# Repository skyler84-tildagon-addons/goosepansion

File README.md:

# Goosepansion

*Tildagon Badge Hexpansion by Skyler84*

The **Goosepansion** hexpansion is a capacitive touch addon for the Tildagon badge. Additionally it is designed to be reversible - it can be inserted in either orientation to alter the behaviour of the hexpansion!

## **IMPORTANT**

The hardware of the original Goosepansion had some issues with the active electronics. This is being investigated and a bodge fix will hopefully be released soon!

## Hardware

The goosepansion contains some active electronics that are supposed to allow it to be inserted in either orientation. This is achieved by switching two pairs of pass-fets acting as level shifters and *should* allow the I2C bus to work in either orientation. This had some issues in the original board which is being tested and updated.

### BOM

- 2 * [DMG6602SVTQ-7 complementary PN mosfet pair](https://www.mouser.co.uk/ProductDetail/Diodes-Incorporated/DMG6602SVTQ-7?qs=s5XU71A7K7%252BjMAi7Ml65qw%3D%3D)
- 2 * [DMN63D8LDW-7 dual n-channel mosfet](https://www.mouser.co.uk/ProductDetail/Diodes-Incorporated/DMN63D8LDW-7?qs=wo71MgyKIyE2w30D2buODQ%3D%3D)
- 1 * [M24C64-RDW6TP 8KB I2C EEPROM](https://www.mouser.co.uk/ProductDetail/STMicroelectronics/M24C64-RDW6TP?qs=sGAEpiMZZMutXGli8Ay4kLhq6qGQloYzVbuldgB1vR8%3D)
- 2 * 0603 LED
- 2 * current limiting resistors for LEDs
- 5 * 1k resistors
- 1 * 100k resistor

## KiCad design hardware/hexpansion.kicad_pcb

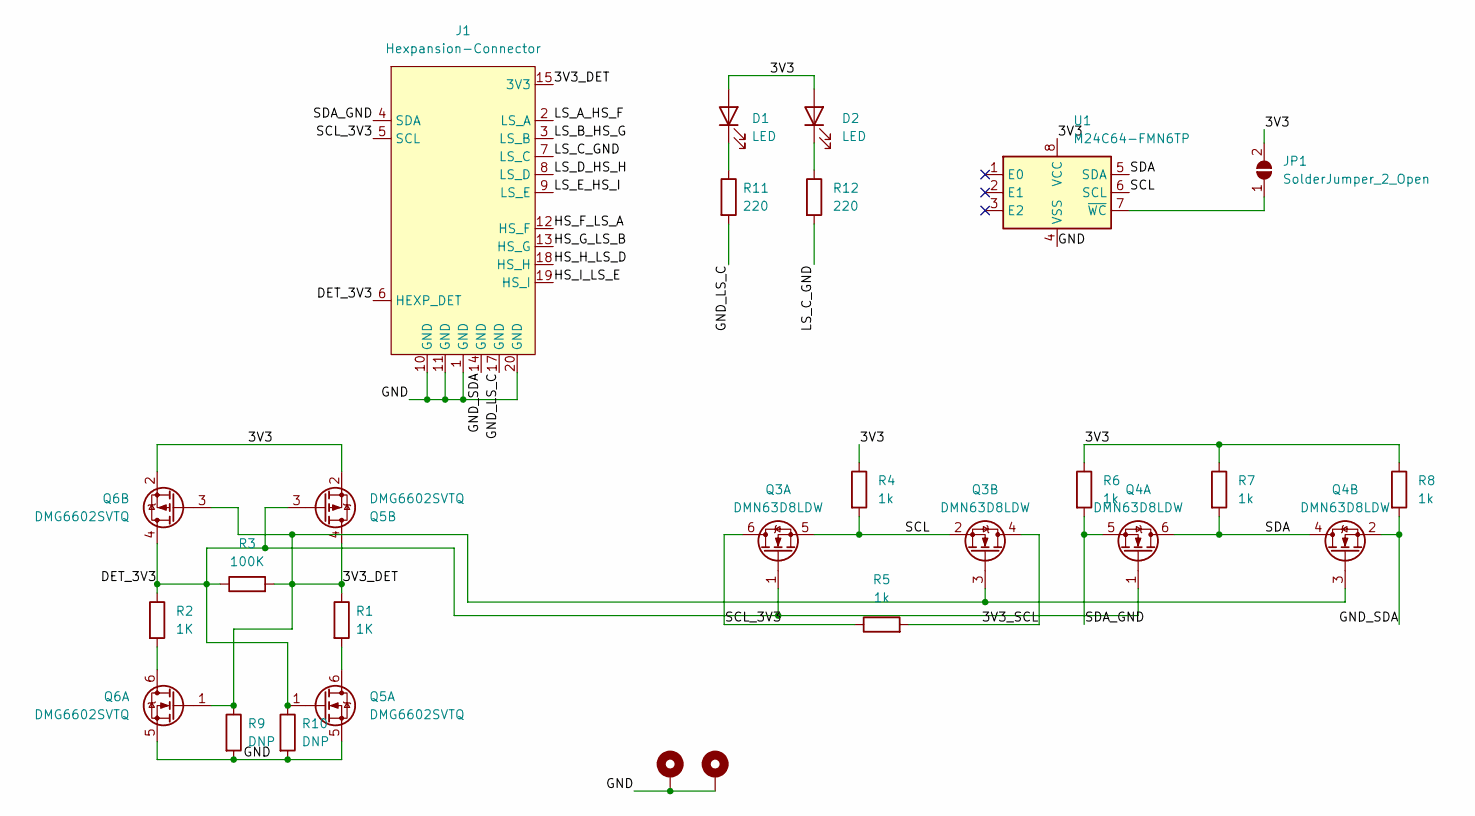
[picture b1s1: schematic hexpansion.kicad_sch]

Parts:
D1, D2: LED; LED_0603_1608Metric_Pad1.05x0.95mm_HandSolder
H1, H2: MountingHole_Pad; MountingHole_2.2mm_M2_Pad_Via
J1: Hexpansion-Connector; hexpansion-edge-connector
JP1: SolderJumper_2_Open; SolderJumper-2_P1.3mm_Open_RoundedPad1.0x1.5mm
Q3, Q4: DMN63D8LDW; SOT-363_SC-70-6
Q5, Q6: DMG6602SVTQ; TSOT-23-6
R1, R2: 1K; R_0603_1608Metric
R3: 100K; R_0603_1608Metric
R4, R5, R6, R7, R8: 1k; R_0603_1608Metric
R9, R10: DNP; R_0603_1608Metric
R11, R12: 220; R_0603_1608Metric
U1: M24C64-FMN6TP; SOIC-8_3.9x4.9mm_P1.27mm

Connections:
/3V3: D1.2 (A), D2.2 (A), JP1.2 (B), Q5.2 (S), Q6.2 (S), R4.1, R6.1, R7.1, R8.1, U1.8 (VCC)
/DET_3V3: J1.6 (HEXP_DET), Q3.1 (G), Q4.1 (G), Q5.1 (G), Q5.3 (G), Q6.4 (D), R2.1, R3.1, R10.1
/GND: H1.1, H2.1, J1.1 (GND), J1.10 (GND), J1.11 (GND), J1.20 (GND), Q5.5 (S), Q6.5 (S), R9.2, R10.2, U1.4 (VSS)
/GND_LS_C: J1.17 (GND), R11.2
/GND_SDA: J1.14 (GND), Q4.2 (S), R8.2
/HS_F_LS_A: J1.12 (HS_F)
/HS_G_LS_B: J1.13 (HS_G)
/HS_H_LS_D: J1.18 (HS_H)
/HS_I_LS_E: J1.19 (HS_I)
/LS_A_HS_F: J1.2 (LS_A)
/LS_B_HS_G: J1.3 (LS_B)
/LS_C_GND: J1.7 (LS_C), R12.2; also elsewhere on the board
/LS_D_HS_H: J1.8 (LS_D)
/LS_E_HS_I: J1.9 (LS_E)
/SCL: Q3.2 (S), Q3.5 (S), R4.2, U1.6 (SCL)
/SCL_3V3: J1.5 (SCL), Q3.6 (D), R5.1
/SDA: Q4.4 (D), Q4.6 (D), R7.2, U1.5 (SDA)
/SDA_GND: J1.4 (SDA), Q4.5 (S), R6.2
unnamed: D1.1 (K), R11.1
unnamed 19: D2.1 (K), R12.1; also elsewhere on the board
unnamed: JP1.1 (A), U1.7 (~WC)
unnamed: Q5.6 (D), R1.2
unnamed: Q6.6 (D), R2.2

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
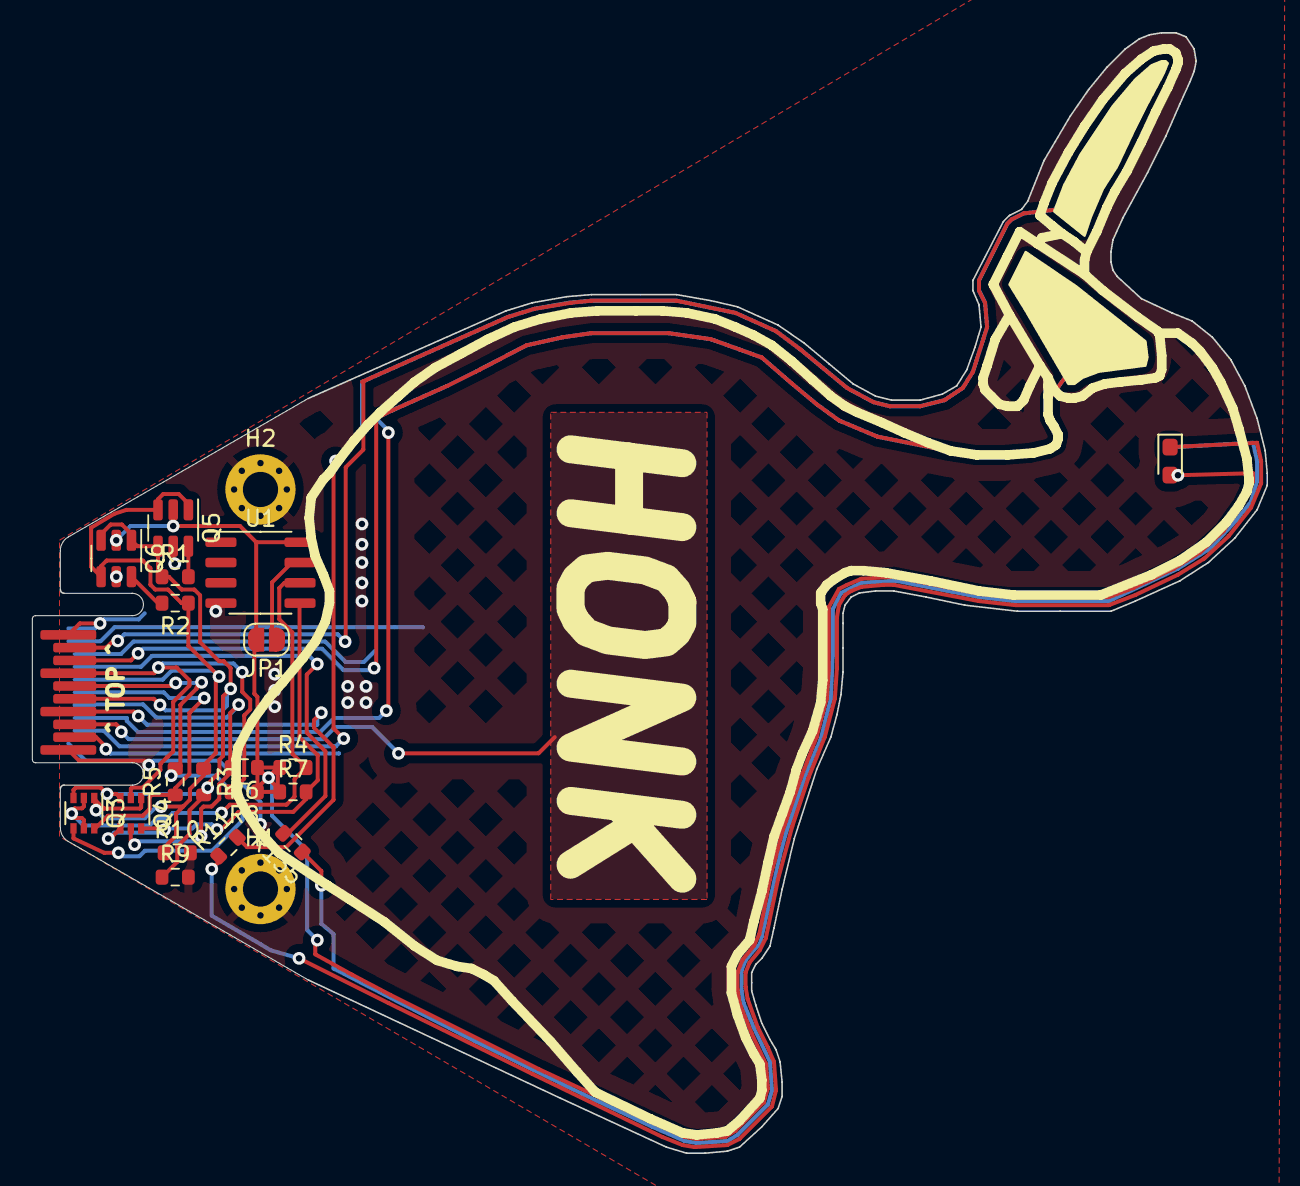
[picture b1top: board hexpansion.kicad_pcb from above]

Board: 2 copper layers, 77.3 x 70.1 mm, 23 parts (1 on the bottom side), 17 nets.

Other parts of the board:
R135: 220; R_0603_1608Metric

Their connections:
/LS_C_GND: R135.2; also elsewhere on the board
unnamed 19: R135.1; also elsewhere on the board

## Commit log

2024-04-17 Initial commit of Goosepansion!
    Currently just the PCB design as I haven't started with the software yet!
2024-06-06 Add README
    Add readme with initial information on Goosepansion
